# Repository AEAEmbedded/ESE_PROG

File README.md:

# ESE_PROG - Programming 5 / 6 (2026-2027)

Course repository for **Programming 5 (Prog 5)** and **Programming 6 (Prog 6)** of the
Embedded Systems Engineering track, Software Engineering, HAN University of Applied Sciences.

| Course | Period | When | Folder |
| --- | --- | --- | --- |
| **Prog 5** | Period 1 | September - October 2026 | [`Prog5/`](Prog5/) - lectures, labs, assignments, example code |
| **Prog 6** | Period 2 | November 2026 - January 2027 | [`Prog6/`](Prog6/) - workshops, Hackathon, Challenge, rubrics |

## Welcome to Prog 5

Prog 5 and Prog 6 are the final lap of the programming courses in your ESE journey. Together they
work towards one overall goal: **becoming a professional embedded software and systems developer**.

Prog 5 (period 1) is about object-oriented C++ on microcontrollers (Arduino / SAMD21) and on the
Raspberry Pi: writing sensor libraries, designing them with UML, connecting them to the outside
world (I2C, MQTT) and testing them. Prog 6 (period 2) builds on that with software-engineering
practice - build systems, unit testing, clean code and design patterns - and applies it in the
Hackathon and the Challenge project.

### Why everything is done with Git

All work in Prog 5 and 6 is done with **Git**, because it is the only way to reach our learning
goals. Git:

* lets several developers work on the same project at the same time;
* keeps a complete history of every change to the code;
* makes it easy to revert a change or recover an earlier version;
* helps you resolve conflicts between contributions efficiently.

More importantly, it takes you out of an artificial learning environment and into the professional
field: the companies where you will do your internship and, later, land a job use exactly these
tools. Being fluent in them is part of being a professional - see
[Coder vs Developer vs Software Engineer: what's the difference?](https://youtu.be/fcjBfSiyI0k)

### Handing in your work

Put your assignments in a (private) Git repository and add your lecturer as a collaborator
(GitHub username **jakorten**). Commit as you go - a
repository with a real history of small, meaningful commits is part of what is assessed.

## Prog 5 schedule and deadlines (period 1, 2026-2027)

The course starts on **Thursday 3 September 2026** and runs for seven weeks. Every week combines
one design principle, a C++ topic and a UML topic, and every Friday there is a lab. The first two
labs are Git and Requirements; from week 3 onwards the Friday lab is the next step of **one sensor
library** that grows week by week (the BME280 is the concrete sensor we use; another I2C sensor
works just as well). The same seven-step plan is on the schedule slide of every lecture deck.

| Week | Lecture (Thu) | Design principle | C++ | UML | Slides | Lab (Fri) |
| :-: | --- | --- | --- | --- | --- | --- |
| 1 | 3 Sep 2026 | Single Responsibility | Scope, namespaces, string | Use cases / class diagram | [0. Course introduction](Prog5/Keynotes/), [1. Introduction](Prog5/Keynotes/) | Fri 4 Sep: [Git workshop 1](Prog5/Workshops/Git/Workshop1_Basics.md) - the basics (clone, add, commit, push, .gitignore, handing in) |
| 2 | 10 Sep 2026 | Open-Closed Principle | Constructors, iterators, lambdas | Inheritance / generalization | [2. Constructors and more](Prog5/Keynotes/) | Fri 11 Sep: Requirements (SMART, FURPS+, MoSCoW, use cases) |
| 3 | 17 Sep 2026 | Liskov Substitution Principle | Lists, inline functions, default params | Activity diagrams | [3. Lists, inline functions and default params](Prog5/Keynotes/) | Fri 18 Sep: sensor library 1 - core, `Bus`, Arduino |
| 4 | 24 Sep 2026 | Interface Segregation Principle | Interfaces and abstract classes | Dependencies | [4. Interfaces and abstract classes](Prog5/Keynotes/) | Fri 25 Sep: sensor library 2 - Raspberry Pi, `Bus` / `Clock` split |
| 5 | 1 Oct 2026 | Dependency Inversion Principle | Threads, callbacks | Sequence diagrams | [5. Threading and callbacks](Prog5/Keynotes/) | Fri 2 Oct: sensor library 3 - sampler thread, callback, MQTT |
| 6 | 8 Oct 2026 | Coupling and cohesion | Polymorphism | Composition, packages | [6. Polymorphism](Prog5/Keynotes/) | Fri 9 Oct: sensor library 4 - polymorphism, UML design |
| 7 | 15 Oct 2026 | Embedded SOLID | Lifecycle: constructors, destructors, const | - | [7. Lifecycle](Prog5/Keynotes/) | Fri 16 Oct: sensor library 5 - RAII, host unit tests, refactor |

Each assignment is introduced in the lecture of the week listed below and is due **one week
later, on the Thursday of the following week**. Full hand-outs: [`Prog5/Assignments/`](Prog5/Assignments/).

| Week | Lecture | Assignment | Deadline |
| :-: | --- | --- | --- |
| 1 | Thu 3 Sep 2026 | **1.** Make a basic stepper motor library and hand it in via your Git repository. | Thu 10 Sep 2026 |
| 2 | Thu 10 Sep 2026 | **2.** Create a UML use-case diagram with description for a sensor application (e.g. KNMI / weather station). | Thu 17 Sep 2026 |
| 3 | Thu 17 Sep 2026 | **3.** [Sensor library, core + Arduino](Prog5/Assignments/week3/bme280_arduino_library.md): Bosch driver wrapped in a class, `Bus` interface, `ArduinoI2cBus`, example sketch. Tag `v0.3-arduino`. | Thu 24 Sep 2026 |
| 4 | Thu 24 Sep 2026 | **4.** [Same library on the Raspberry Pi](Prog5/Assignments/week4/bme280_raspberry_pi.md): CMake build, `LinuxI2cBus`, `Bus` / `Clock` split (ISP), dependency diagram. Tag `v0.4-pi`. | Thu 1 Oct 2026 |
| 5 | Thu 1 Oct 2026 | **5.** [Sampling thread, callback, MQTT](Prog5/Assignments/week5/bme280_mqtt.md): `Sampler`, `Publisher` / `MqttPublisher`, `EnvironmentSensor` + `FakeSensor`, sequence diagram sketch. Tag `v0.5-mqtt`. | Thu 8 Oct 2026 |
| 6 | Thu 8 Oct 2026 | **6.** [Design on paper](Prog5/Assignments/week6/bme280_uml_design.md): class, package and sequence diagrams of the library; `vector<EnvironmentSensor*>` with a second sensor. Tag `v0.6-design`. | Thu 15 Oct 2026 |
| 7 | Thu 15 Oct 2026 | **7.** [Unit tests on the host](Prog5/Assignments/week7/bme280_tests_and_refactor.md) with the `MockBus` (no mocking framework yet). <br> **8.** Review the library against DRY, KISS, SOLID, coupling / cohesion and the lifecycle checklist; add a second sensor and move the shared abstractions (`Bus`, `Clock`, `EnvironmentSensor`) into their own package; refactor and report. Tag `v1.0`. | Thu 22 Oct 2026 |

**Resit:** assignments that were not handed in on time, or that did not pass, can be (re)submitted
until the resit deadline of **Thursday 29 October 2026**.

Assignments 3-8 all build on the same sensor library (the Friday labs are its steps), so keep it in one repository and let its
history show how it grows: from a first Arduino version to a tested, refactored Pi library that
publishes over MQTT. Starter code per week is in [`Prog5/Code/`](Prog5/Code/) (`week2`: the
wrapper library, `week4`: Linux I2C bus, `week5`: sampler + MQTT).

## Learning outcomes

The learning outcomes below follow the HAN engineering competencies used in the rubrics
(*Analyze - Design - Manage - Control - Realize - Professionalize*). Prog 5 lays the foundation;
Prog 6 raises every outcome to a professional level and assesses it in the Hackathon and the
Challenge.

### Prog 5 - after period 1 you can

| # | Learning outcome | Competency |
| :-: | --- | --- |
| P5.1 | **Analyse** a realistic problem into user stories and SMART requirements, categorised with FURPS+ and prioritised with MoSCoW. | Analyze |
| P5.2 | **Design** software with UML: a use-case diagram with descriptions, a class diagram and a sequence diagram (and a state diagram where behaviour asks for it). | Design |
| P5.3 | **Implement** object-oriented C++ on embedded targets (Arduino / SAMD21 and Raspberry Pi): classes and encapsulation, constructors/destructors and object lifecycle, inheritance, abstract classes and interfaces, polymorphism, smart pointers, lambdas and callbacks, basic concurrency. | Realize |
| P5.4 | **Build reusable sensor libraries**: an Arduino library for an (I2C) sensor, a C++ library for an I2C sensor on the Raspberry Pi, and connect it to an MQTT broker. | Realize |
| P5.5 | **Apply DRY, KISS, SOLID and loose coupling / strong cohesion**, recognise where your own code violates them, refactor it and explain what improved. | Realize |
| P5.6 | **Test** a library with basic unit tests in C++. | Control |
| P5.7 | **Use Git professionally** for all your work: meaningful commits, branches, pull requests and a readable history, in a repository you share with your lecturer. | Manage |

### Prog 6 - after period 2 you can

| # | Learning outcome | Competency |
| :-: | --- | --- |
| P6.1 | **Set up and maintain a CMake build** for a C/C++ project with its own libraries and externally fetched test dependencies, and explain why build systems exist. | Realize |
| P6.2 | **Unit test at a professional level** with CppUTest, including test doubles and mocks for hardware dependencies, and position tests in the testing pyramid. | Control |
| P6.3 | **Write clean, well-commented, maintainable code**: recognise code smells, apply MISRA C++:2023 guidelines and use static-analysis tooling to check your own code. | Realize |
| P6.4 | **Apply embedded design patterns and architecture** (state, observer, hardware proxy, cyclic executive, debouncing, fixed-point arithmetic, humble object) with awareness of their run-time and memory overhead. | Design |
| P6.5 | **Realise a working proof-of-concept** for a healthcare case (Wilhelmina Children's Hospital, WKZ) - in a team under time pressure in the Hackathon and in the longer Challenge project - from analysis and SOLID design, through technical designs (class, sequence, state), to a tested implementation. | Analyze / Design / Realize |
| P6.6 | **Manage code as a team** in Git with commits, pull requests, blame and code reviews throughout the project. | Manage |
| P6.7 | **Reflect and advise**: give substantiated advice based on your analysis and proof-of-concept and present it convincingly (presentation, report or video), communicating professionally with the team, lecturers and domain experts. | Professionalize |

Assessment: Prog 5 by the weekly assignments (see schedule below); Prog 6 with the
[Hackathon and Prog 6 rubrics](Prog6/Rubrics/).

## Repository layout

| Folder | Contents |
| --- | --- |
| [`Prog5/Keynotes/`](Prog5/Keynotes/) | Lecture slides (PDF): course introduction and lectures 1-7. |
| [`Prog5/Labs/`](Prog5/Labs/) | Lab hand-outs (Lab 2: Arduino basics with OOP / SOLID; Lab 3: I2C sensor library). |
| [`Prog5/Assignments/`](Prog5/Assignments/) | Assignment hand-outs per week; from week 3 on all steps of the one sensor library (BME280 as the worked example). |
| [`Prog5/Code/week1/`](Prog5/Code/week1/) | Week 1 example code: stepper motor examples, `SimpleStepper` library, TB6600 test. |
| [`Prog5/Code/week2/`](Prog5/Code/week2/) | BME280 starter library: `Bus` interface, wrapper around the vendored Bosch BME280 SensorAPI, `MockBus` + doctest. |
| [`Prog5/Code/week4/`](Prog5/Code/week4/) | `rpi_platform`: `LinuxI2cBus` on `/dev/i2c-1` and a smoke test, CMake build of core + platform. |
| [`Prog5/Code/week5/`](Prog5/Code/week5/) | `mqtt_station`: `EnvironmentSensor`, `Sampler` (thread + callback), `Publisher` / `MqttPublisher` (libmosquitto), composition root. |
| [`Prog5/Code/Examples/`](Prog5/Code/Examples/) | Demo code used in the lectures and labs (abstract interfaces, object lifecycle, ToF sensor library, SOLID terminal, I2C scanner). |
| [`Prog5/Workshops/Git/`](Prog5/Workshops/Git/) | Git workshops 1 (the basics) and 2 (working together), with an interactive version. |
| [`Prog5/Demos/`](Prog5/Demos/) | Hand-outs: Git manual, CMake basics, interfaces demo. |
| [`Prog6/Workshops/`](Prog6/Workshops/) | Workshops: CMake, Unit Testing (CppUTest), Commenting, Clean Code / MISRA C++, Design Patterns & Architecture. |
| [`Prog6/Hackathon/`](Prog6/Hackathon/) | Hackathon material: the VitalSignsBox modules (ECG lead detection, SpO2 detection, temperature sensors) with firmware, API descriptions and hardware files. |
| [`Prog6/Challenge/`](Prog6/Challenge/) | Challenge project: assignment document and hardware design files (SensorHub, ActuatorHub, sim modules, adapters). |
| [`Prog6/Rubrics/`](Prog6/Rubrics/) | Assessment rubrics 2026-2027 (Prog 6 v1.5, Hackathon v1.4; Markdown source + PDF) and previous editions. |
| [`Resources/`](Resources/) | Background reading, e.g. choosing a development method. |

## How to use

1. Clone the repository: `git clone https://github.com/AEAEmbedded/ESE_PROG`
2. Arduino sketches (`*.ino`): open the sketch folder in the Arduino IDE and upload to your board.
3. CMake projects (workshops): configure out-of-source, e.g.
   ```bash
   cmake -S Prog6/Workshops/UnitTesting/Source/TemperatureTestFinished -B build
   cmake --build build
   ctest --test-dir build
   ```
   Build directories are ignored by git - do not commit them.
4. Refer to the keynotes, labs and workshop READMEs for instructions.

## Related repositories

* **[PiTest](https://github.com/jakorten/PiTest)** - Raspberry Pi 4 to SensorHub (SAMD21) I2C communication test (Python for the Pi, C++ Arduino sketches for the SAMD21).

## Disclaimer

This repository is for educational purposes. The code may be incomplete or contain errors. Use at your own risk.

## Contact

Johan Korten - johan.korten@han.nl

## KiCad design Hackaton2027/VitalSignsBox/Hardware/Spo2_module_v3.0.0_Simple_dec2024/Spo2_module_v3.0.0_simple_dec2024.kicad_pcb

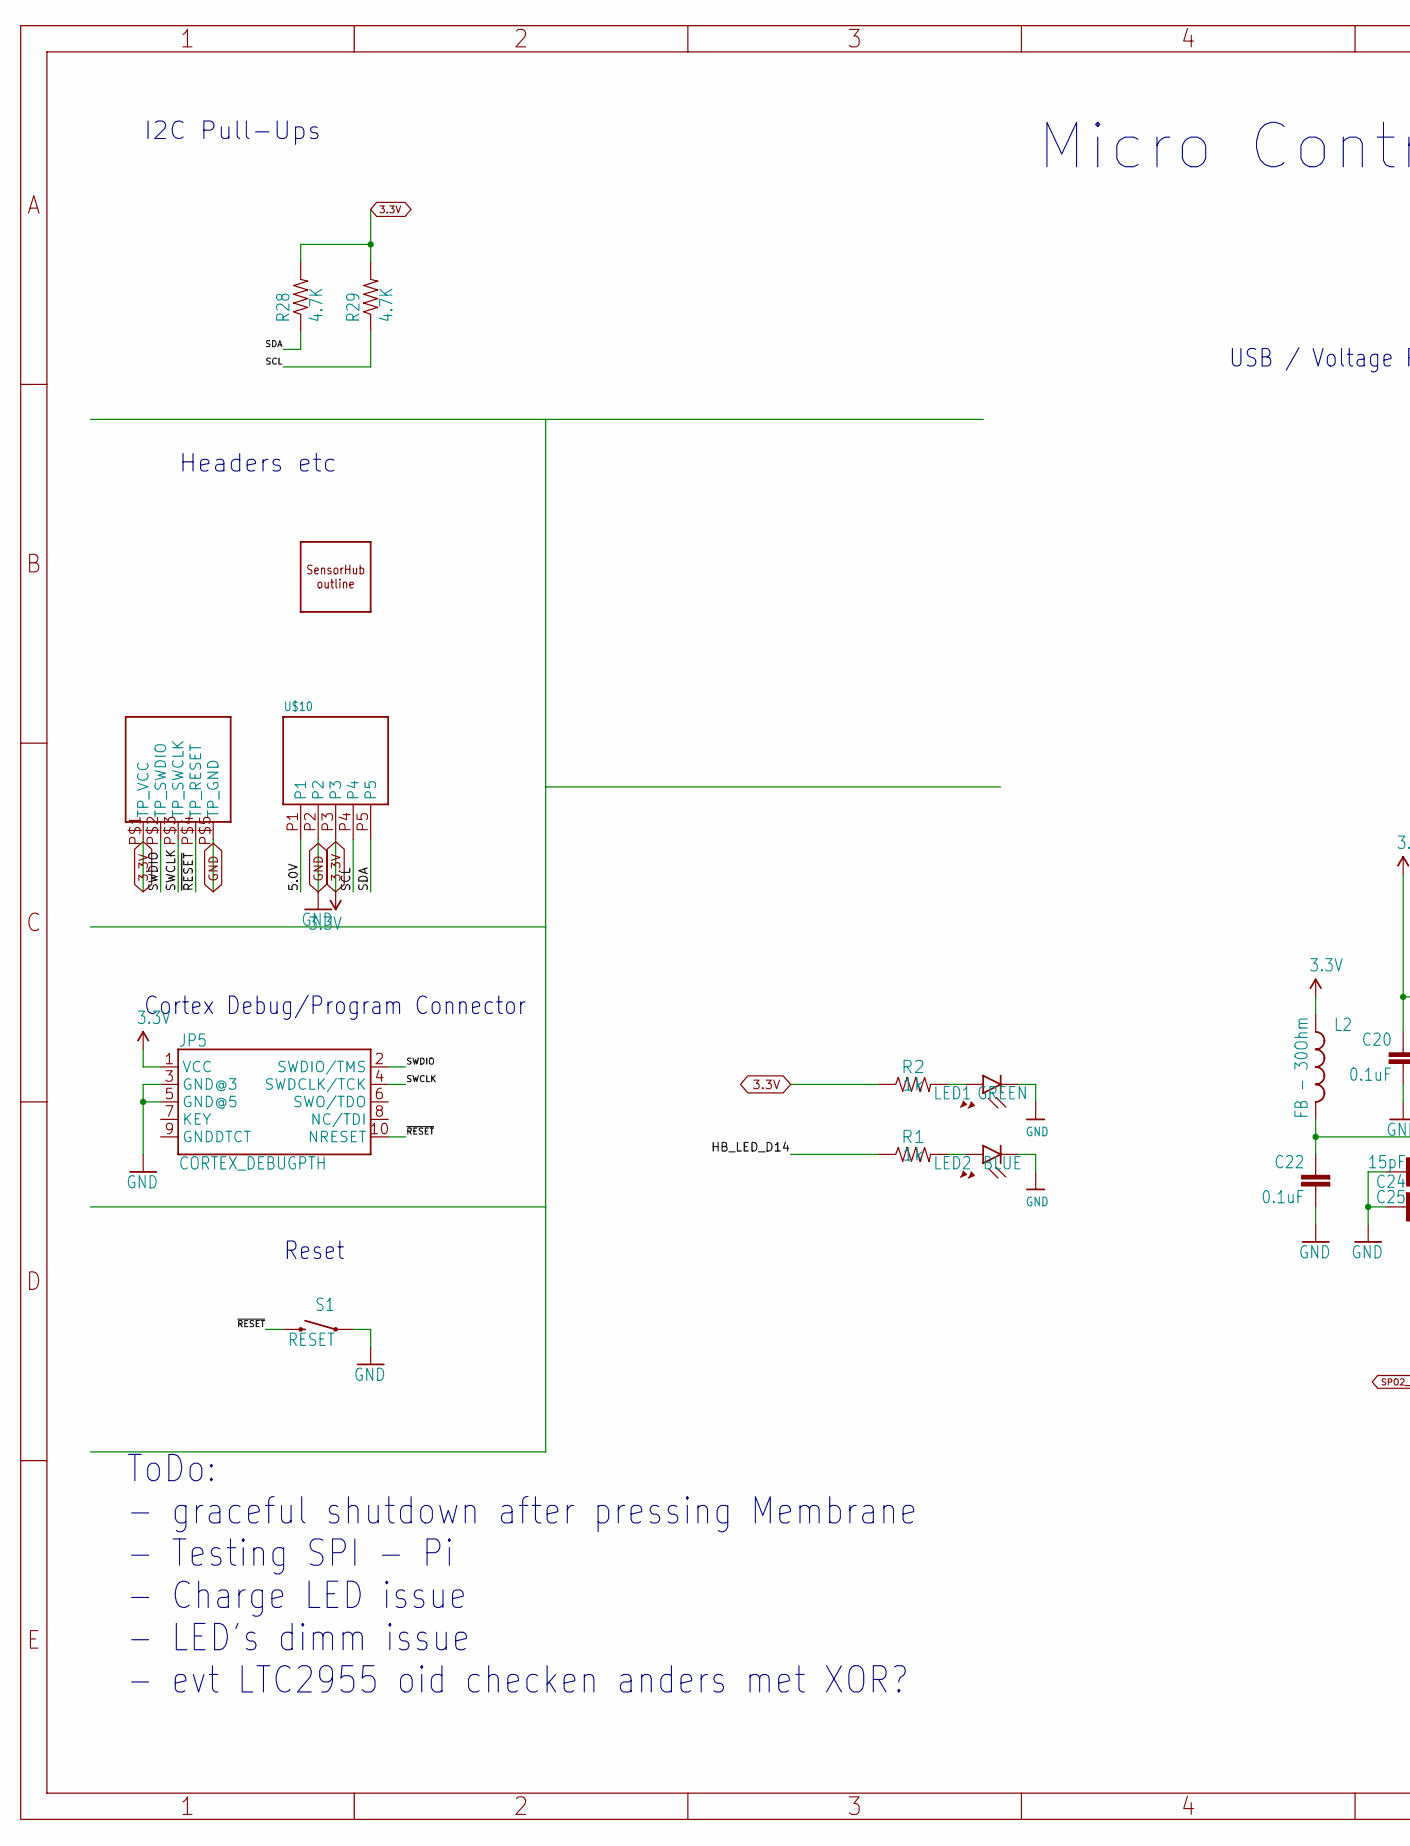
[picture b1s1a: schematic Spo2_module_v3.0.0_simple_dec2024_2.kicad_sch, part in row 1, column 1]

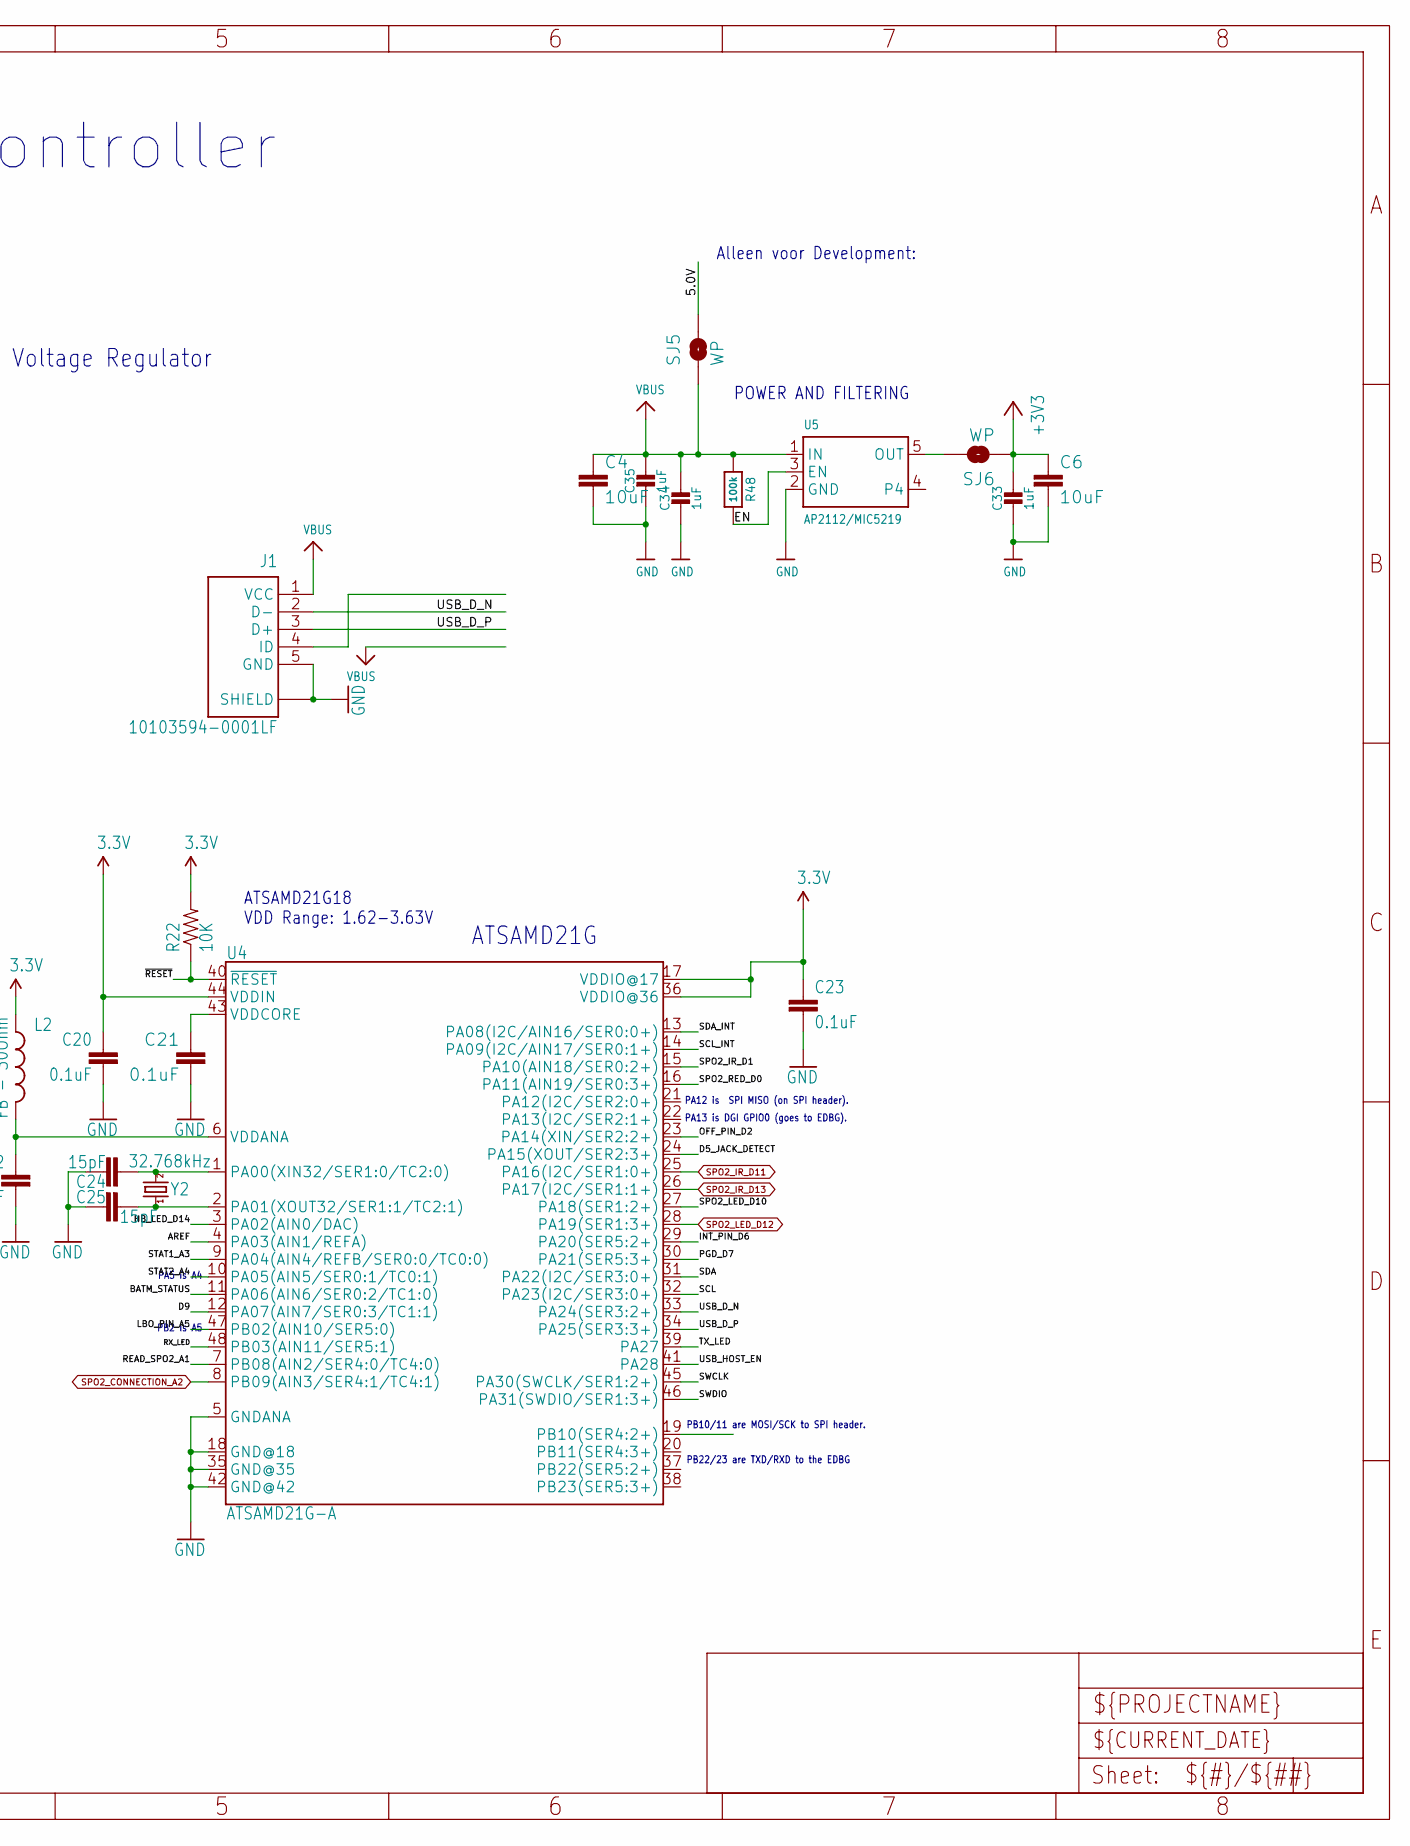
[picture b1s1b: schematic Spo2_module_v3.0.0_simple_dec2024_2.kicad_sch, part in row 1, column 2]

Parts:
C4, C6: 10uF; 0603
C20, C22, C23: 0.1uF; 0402-CAP
C21: 0.1uF; 0603
C24, C25: 15pF; 0402-CAP
C33, C34, C35: 1uF; 0603-NO
J1: 10103594-0001LF; AMPHENOL_10103594-0001LF
JP5: CORTEX_DEBUGPTH; 2X5-PTH-1.27MM
L2: FB - 30Ohm; 0603
LED1: GREEN; CHIP-LED0603
LED2: BLUE; CHIP-LED0603
R1, R2: 1k; 0603
R22: 10K; 0603-RES
R28, R29: 4.7K; 0603-RES
R48: 100k; 0603-NO@1
S1: RESET; TACTILE_SWITCH_SMD_4.6X2.8MM
SJ5, SJ6: WP; SMT-JUMPER_2_NO_NO-SILK
U4: ATSAMD21G-A; TQFP-48
U5: AP2112/MIC5219; SOT23-5
U$5: HUB_TESTPINSHUBS; TEST_PINS
U$10: PHOENIX_PTSM_M5_TH_I2C++; PTSM_M5_THRHOLE
U$12: SENSORHUB_PROFILEUSB_LEFT; SENSORHUB_OUTLINE_USB_NOTCH_LEFT
Y2: 32.768kHz; CRYSTAL-SMD-3.2X1.5MM

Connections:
5.0V: SJ5.2, U$10.P1
AREF: U4.4 (PA03(AIN1/REFA))
BATM_STATUS: U4.11 (PA06(AIN6/SER0:2/TC1:0))
D5_JACK_DETECT: U4.24 (PA15(XOUT/SER2:3+))
D9: U4.12 (PA07(AIN7/SER0:3/TC1:1))
EN: R48.2, U5.3 (EN)
GND: C4.2, C6.2, C20.2, C21.2, C22.2, C23.2, C24.1, C25.2, C33.2, C34.2, C35.2, J1.5 (GND), J1.6 (SHIELD), J1.7 (SHIELD), J1.8 (SHIELD), J1.9 (SHIELD), J1.10 (SHIELD), J1.11 (SHIELD), J1.S1 (SHIELD), J1.S2 (SHIELD), JP5.3 (GND@3), JP5.5 (GND@5), LED1.C, LED2.C, S1.1, S1.2 (1), U4.5 (GNDANA), U4.18 (GND@18), U4.35 (GND@35), U4.42 (GND@42), U5.2 (GND), U$5.P$5 (TP_GND), U$10.P2; also elsewhere on the board
HB_LED_D14: R1.1, U4.3 (PA02(AIN0/DAC))
INT_PIN_D6: U4.29 (PA20(SER5:2+))
LBO_PIN_A5: U4.47 (PB02(AIN10/SER5:0))
unnamed: LED1.A, R2.2
unnamed: LED2.A, R1.2
unnamed: C24.2, U4.1 (PA00(XIN32/SER1:0/TC2:0)), Y2.P$2 (2)
unnamed: C25.1, U4.2 (PA01(XOUT32/SER1:1/TC2:1)), Y2.P$1 (1)
OFF_PIN_D2: U4.23 (PA14(XIN/SER2:2+))
OUT: SJ6.2, U5.5 (OUT)
PGD_D7: U4.30 (PA21(SER5:3+))
READ_SPO2_A1: U4.7 (PB08(AIN2/SER4:0/TC4:0))
RX_LED: U4.48 (PB03(AIN11/SER5:1))
SCL: R29.1, U4.32 (PA23(I2C/SER3:0+)), U$10.P4
SCL_INT: U4.14 (PA09(I2C/AIN17/SER0:1+))
SDA: R28.1, U4.31 (PA22(I2C/SER3:0+)), U$10.P5
SDA_INT: U4.13 (PA08(I2C/AIN16/SER0:0+))
SPO2_CONNECTION_A2: U4.8 (PB09(AIN3/SER4:1/TC4:1)); also elsewhere on the board
SPO2_IR_D1: U4.15 (PA10(AIN18/SER0:2+))
SPO2_IR_D11: U4.25 (PA16(I2C/SER1:0+)); also elsewhere on the board
SPO2_IR_D13: U4.26 (PA17(I2C/SER1:1+)); also elsewhere on the board
SPO2_LED_D10: U4.27 (PA18(SER1:2+))
SPO2_LED_D12: U4.28 (PA19(SER1:3+)); also elsewhere on the board
SPO2_RED_D0: U4.16 (PA11(AIN19/SER0:3+))
STAT1_A3: U4.9 (PA04(AIN4/REFB/SER0:0/TC0:0))
STAT2_A4: U4.10 (PA05(AIN5/SER0:1/TC0:1))
SWCLK: JP5.4 (SWDCLK/TCK), U4.45 (PA30(SWCLK/SER1:2+)), U$5.P$3 (TP_SWCLK)
SWDIO: JP5.2 (SWDIO/TMS), U4.46 (PA31(SWDIO/SER1:3+)), U$5.P$2 (TP_SWDIO)
TX_LED: U4.39 (PA27)
USB_D_N: J1.2 (D-), U4.33 (PA24(SER3:2+))
USB_D_P: J1.3 (D+), U4.34 (PA25(SER3:3+))
USB_HOST_EN: U4.41 (PA28)
VBUS: C4.1, C34.1, C35.1, J1.1 (VCC), R48.1, SJ5.1, U5.1 (IN)
VDDANA: C22.1, L2.2, U4.6 (VDDANA)
VDDCORE: C21.1, U4.43 (VDDCORE)
~RESET: JP5.10 (NRESET), R22.1, S1.3 (2), S1.4 (2), U4.40 (~RESET), U$5.P$4 (TP_RESET)

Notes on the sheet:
USB / Voltage Regulator
PA5 is A4
ToDo: - graceful shutdown after pressing Membrane - Testing SPI - Pi - Charge LED issue - LED's dimm issue - evt LTC2955 oid checken anders met XOR?
Micro Controller
POWER AND FILTERING
Alleen voor Development:
PB22/23 are TXD/RXD to the EDBG
Headers etc
PA13 is DGI GPIO0 (goes to EDBG).
Cortex Debug/Program Connector
I2C Pull-Ups
PB2 is A5
Reset
ATSAMD21G18 VDD Range: 1.62-3.63V
ATSAMD21G
PA12 is SPI MISO (on SPI header).
PB10/11 are MOSI/SCK to SPI header.

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
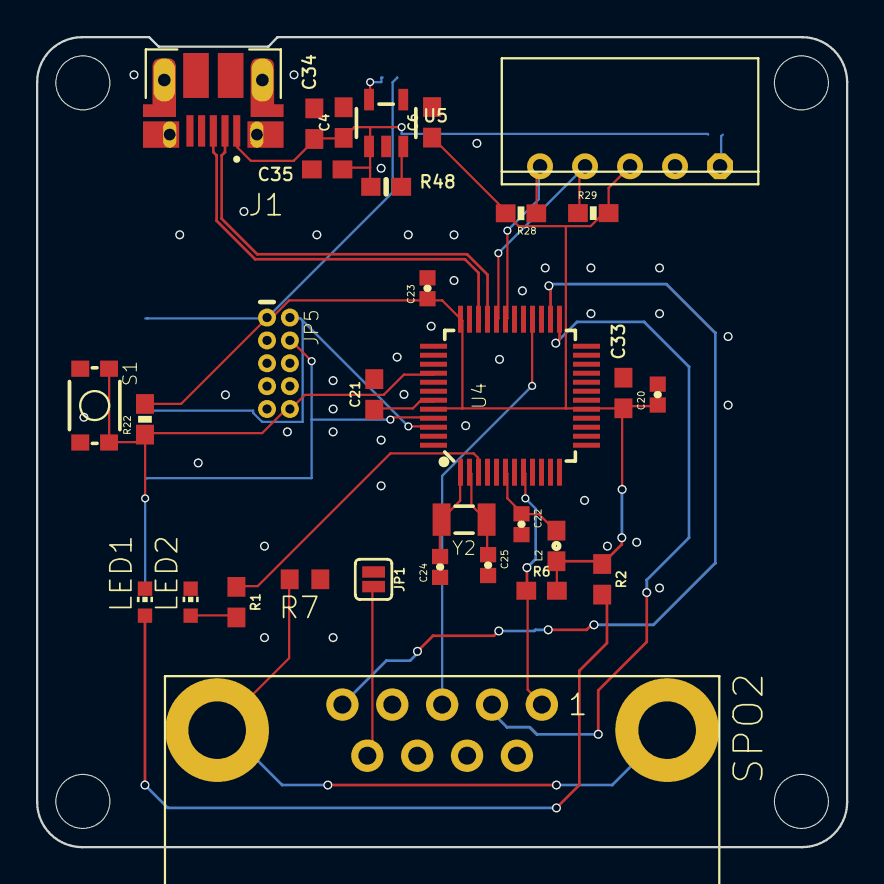
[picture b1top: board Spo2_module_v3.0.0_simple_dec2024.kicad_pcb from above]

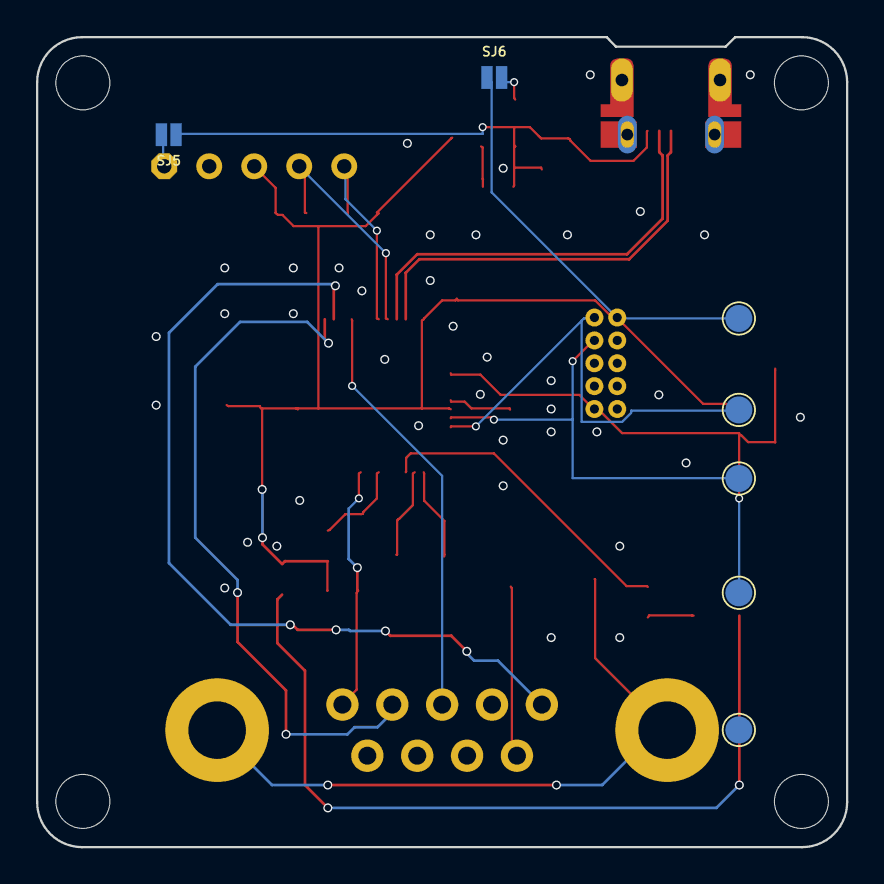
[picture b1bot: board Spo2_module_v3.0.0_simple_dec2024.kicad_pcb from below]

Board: 2 copper layers, 45.0 x 45.0 mm, 35 parts (2 on the bottom side), 26 nets.

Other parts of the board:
JP1: JUMPER-SMT_2_NC_PASTE_SILK; SMT-JUMPER_2_NC_PASTE_SILK_528
R6: 10k; 0603_532
R7: 39Ω; R0603_420
SPO2: 618009231121

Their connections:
GND: JP1.1, R7.1, SPO2.6, SPO2.7; also elsewhere on the board
unnamed: R7.2, SPO2.SHELL, SPO2.SHELL1
SPO2_CATHODE: JP1.2, SPO2.9
SPO2_CONNECTION_A2: R6.1, SPO2.1; also elsewhere on the board
SPO2_IR_D11: SPO2.2; also elsewhere on the board
SPO2_IR_D13: SPO2.5; also elsewhere on the board
SPO2_LED_D12: SPO2.3; also elsewhere on the board

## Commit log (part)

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2024-09-20 Updated slides lecture 3
2024-09-20 Changed folder name old rubrics
2024-09-20 Lab week 3
2024-09-20 bugfix: fixed phony parameter in scanForDevice in the VL6180XScanner class
2024-09-20 Added Wirescanner Library for Arduino
2024-09-26 Updated presentations
2024-09-26 Added manuals
2024-09-26 Week 4 updates
2024-09-30 Updated demo etc
2024-09-30 Updated lecture 5 keynote
2024-10-17 Updated keynotes
2024-11-14 Added new rubrics Prog 6
2024-11-21 Added hardware schematics and boards (Eagle)
2024-11-22 Improved name giving
2024-11-22 Delete HAN_Hackaton_Prog_6_2025.pdf
    Renamed Hackathon to Challenge to avoid confusion...
2024-11-22 Added link to Patient Monitor
2024-11-28 Added more hardware and PDF version of schematics
2025-09-04 Update for 2025-2026
2025-09-04 Examples week 1
2025-09-04 Added some hints etc
2025-09-05 Added assignment week 2
2025-09-12 Updated lecture keynotes week 2
2025-09-12 Added whitepaper development methods
2025-09-12 Added whitepaper development methods (NL)
2025-09-12 Added whitepaper development methods (EN)
2025-09-12 Added whitepaper development methods link to presentation
2025-11-17 Added Clean Code workshop details
2025-11-18 Added Code Smell scanner
2025-11-20 Refactored python / SOLID
2025-11-20 Keynote of the workshop on Clean Code
2025-11-20 Added keynote
2025-11-23 Workshop CMake
2025-11-23 Enh improved CMake workshop
2025-11-23 Enh Embedded CMake and updated keynotes
2025-11-30 Unit Testing basics
2025-11-30 Case 2
2025-11-30 Finished Unit Testing
2025-11-30 Added Workshop commenting
2025-12-02 Enh Workshop commenting
2025-12-08 Added source files for hackaton
2025-12-10 minor changes
2025-12-18 Added updated rubrics
2026-01-04 Added Design Patterns update
2026-01-27 Additional info hackaton hw
